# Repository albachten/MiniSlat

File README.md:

# MiniSlat - 2 cue pyro slat

This is an ARM Cortex M0 board with:
* SAMD21 cpu
* USB for programming & serial debug
* Cortex Debug connector for bootloader install & hw debug
* 2 Pairs of PyroClips (2 cues)
* 915MHz HopeRF RFM95 Lora module
* 2S 18650 LiPo supply (two cells in series) with safe/armed power switch
* INA219 current sensing for continuity test & fire monitoring
* 2 NeoPixels as per-cue status indicators
* I2C expansion (QWIIC connector & 4-pin header)

See [SOFTWARE_SPEC.md](SOFTWARE_SPEC.md) for pin assignments, I2C addresses, and firmware requirements.

[Schematic pdf](v1.0/MiniSlat.pdf)

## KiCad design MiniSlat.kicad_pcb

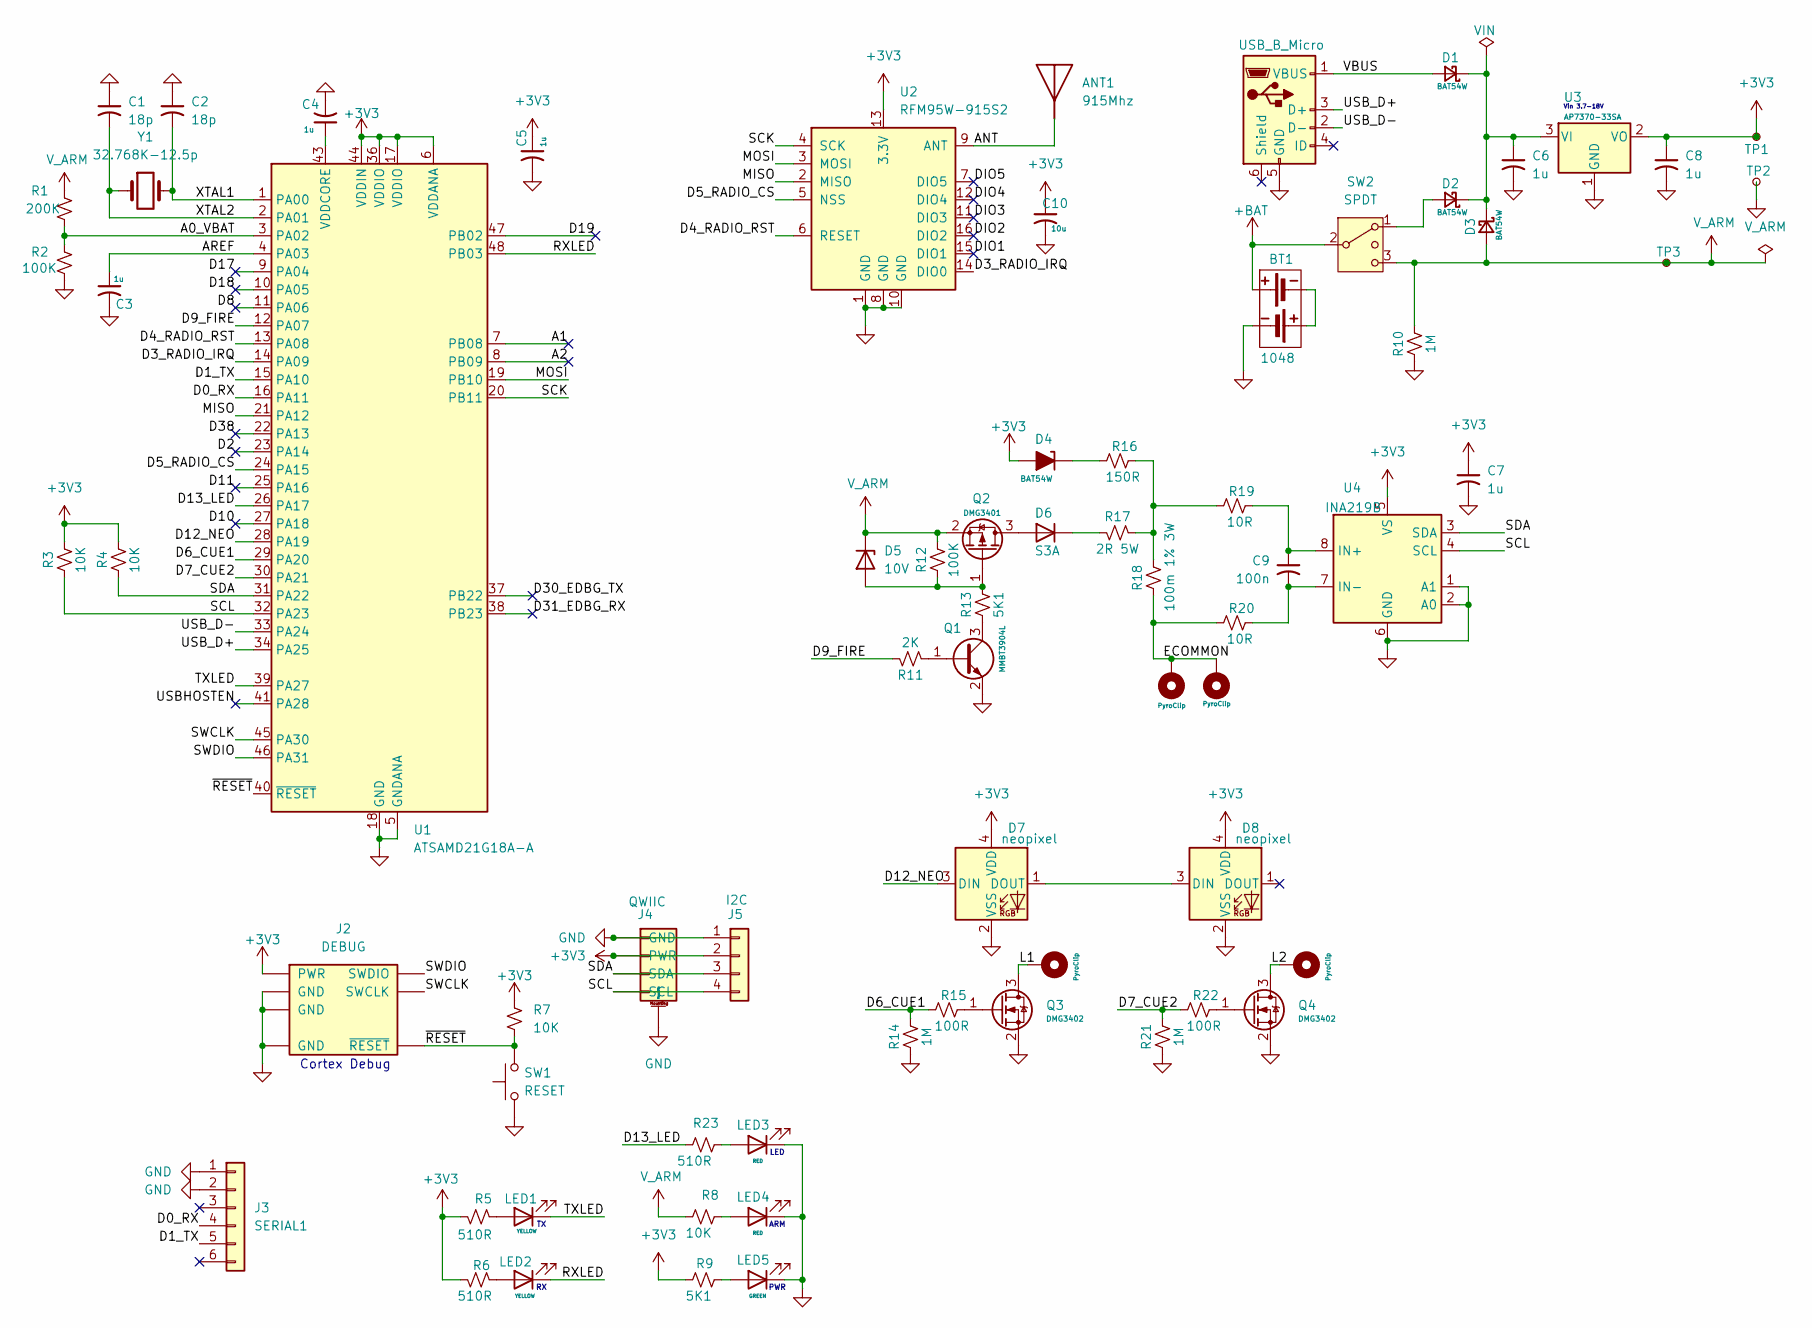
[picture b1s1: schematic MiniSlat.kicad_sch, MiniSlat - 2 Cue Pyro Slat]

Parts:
ANT1: 915Mhz; Antenna915MHzSimpleCoil; Manufacturer_Part_Number 4269; Mouser_Part_Number 485-4269
BT1: 1048; BAT_1048P
C1, C2: 18p; C_0603_1608Metric
C3, C4, C5, C6, C7, C8: 1u; C_0603_1608Metric
C9: 100n; C_0603_1608Metric
C10: 10u; C_0603_1608Metric
CLIP1, CLIP3: PyroClip; PyroClipRed; Mouser_Part_Number N/A
CLIP2, CLIP4: PyroClip; PyroClipBlack; Mouser_Part_Number N/A
D1, D2, D3, D4: BAT54W; D_SOD-123; Mouser_Part_Number 78-BAT54W-HG3-18
D5: 10V; SOT-23; Mouser_Part_Number 863-BZX84C10LT1G
D6: S3A; D_SMC; Mouser_Part_Number 512-S3A
D7, D8: neopixel; LED_WS2812B-2020_PLCC4_2.0x2.0mm
J1: USB_B_Micro; USB_Micro-B_Amphenol_10118194_Horizontal; Mouser_Part_Number 649-10118194-0011LF
J2: DEBUG; CortexDebugSMD; Mouser_Part_Number 640-BD12510A305580LB
J3: SERIAL1; PinHeader_1x06_P2.54mm_Vertical
J4: QWIIC; QWIIC_JST_SH_BM04B-SRSS-TB_1x04-1MP_P1.00mm_Vertical
J5: I2C; PinHeader_1x04_P2.54mm_Vertical
LED1, LED2: YELLOW; LED_0805_2012Metric; Mouser_Part_Number 710-150080YS75000
LED3, LED4: RED; LED_0805_2012Metric; Mouser_Part_Number 710-150080RS75000
LED5: GREEN; LED_0805_2012Metric; Mouser_Part_Number 710-150080RS75000
Q1: MMBT3904L; SOT-23; Mouser_Part_Number 771-MMBT3904VL
Q2: DMG3401; SC-59; Mouser_Part_Number 621-DMP3099L-13
Q3, Q4: DMG3402; SOT-23; Mouser_Part_Number 621-DMG3402L-7
R1: 200K; R_0603_1608Metric
R2, R12: 100K; R_0603_1608Metric
R3, R4, R7, R8: 10K; R_0603_1608Metric
R5, R6, R23: 510R; R_0603_1608Metric
R9, R13: 5K1; R_0603_1608Metric
R10, R14, R21: 1M; R_0603_1608Metric
R11: 2K; R_0603_1608Metric
R15, R22: 100R; R_0603_1608Metric
R16: 150R; R_0603_1608Metric
R17: 2R 5W; R_Axial_Power_L25.0mm_W6.4mm_P27.94mm; Mouser_Part_Number 588-TUW5J2R0E
R18: 100m 1% 3W; R_2512_6332Metric
R19, R20: 10R; R_0603_1608Metric
SW1: RESET; TL3305B_SPST_PushButton; Mouser_Part_Number 652-CR0805JW-104ELF
SW2: SPDT; spdt_100SP1T1B2M2QE
TP1, TP2, TP3: RCTCTE; Mouser_Part_Number 660-RCTCTE
U1: ATSAMD21G18A-A; TQFP-48_7x7mm_P0.5mm; Mouser_Part_Number 556-ATSAMD21G18A-MU
U2: RFM95W-915S2; RFM95CW; Mouser_Part_Number 223-RFM95W-915S2
U3: AP7370-33SA; TSOT-23
U4: INA219B; SOIC-8_3.9x4.9mm_P1.27mm; Mouser_Part_Number 595-INA219BIDR
Y1: 32.768K-12.5p; Crystal_SMD_G8-2Pin_3.2x1.5mm; Mouser_Part_Number 520-327-12.5-34B

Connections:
+3V3: C5.1, C7.1, C8.1, C10.1, D4.2 (A), D7.4 (VDD), D8.4 (VDD), J2.1 (PWR), J4.2 (PWR), J5.2, R3.2, R4.2, R5.1, R6.1, R7.2, R9.1, TP1.1, U1.6 (VDDANA), U1.17 (VDDIO), U1.36 (VDDIO), U1.44 (VDDIN), U2.13 (3.3V), U3.2 (VO), U4.5 (VS)
+BAT: BT1.1, SW2.2 (3)
/A0_VBAT: R1.2, R2.1, U1.3 (PA02)
/A1: U1.7 (PB08)
/A2: U1.8 (PB09)
/ANT: ANT1.1 (A), U2.9 (ANT)
/AREF: C3.1, U1.4 (PA03)
/D0_RX: J3.4, U1.16 (PA11)
/D1_TX: J3.5, U1.15 (PA10)
/D2: U1.23 (PA14)
/D3_RADIO_IRQ: U1.14 (PA09), U2.14 (DIO0)
/D4_RADIO_RST: U1.13 (PA08), U2.6 (RESET)
/D5_RADIO_CS: U1.24 (PA15), U2.5 (NSS)
/D6_CUE1: R14.2, R15.1, U1.29 (PA20)
/D7_CUE2: R21.2, R22.1, U1.30 (PA21)
/D8: U1.11 (PA06)
/D9_FIRE: R11.1, U1.12 (PA07)
/D10: U1.27 (PA18)
/D11: U1.25 (PA16)
/D12_NEO: D7.3 (DIN), U1.28 (PA19)
/D13_LED: R23.1, U1.26 (PA17)
/D17: U1.9 (PA04)
/D18: U1.10 (PA05)
/D19: U1.47 (PB02)
/D30_EDBG_TX: U1.37 (PB22)
/D31_EDBG_RX: U1.38 (PB23)
/D39: U1.22 (PA13)
/DIO1: U2.15 (DIO1)
/DIO2: U2.16 (DIO2)
/DIO3: U2.11 (DIO3)
/DIO4: U2.12 (DIO4)
/DIO5: U2.7 (DIO5)
/ECOMMON: CLIP1.1, CLIP3.1, R18.1, R20.1
/L1: CLIP2.1, Q3.3 (D)
/L2: CLIP4.1, Q4.3 (D)
/MISO: U1.21 (PA12), U2.2 (MISO)
/MOSI: U1.19 (PB10), U2.3 (MOSI)
/RXLED: LED2.1 (K), U1.48 (PB03)
/SCK: U1.20 (PB11), U2.4 (SCK)
/SCL: J4.4 (SCL), J5.4, R3.1, U1.32 (PA23), U4.4 (SCL)
/SDA: J4.3 (SDA), J5.3, R4.1, U1.31 (PA22), U4.3 (SDA)
/SWCLK: J2.4 (SWCLK), U1.45 (PA30)
/SWDIO: J2.2 (SWDIO), U1.46 (PA31)
/TXLED: LED1.1 (K), U1.39 (PA27)
/USBHOSTEN: U1.41 (PA28)
/USB_D+: J1.3 (D+), U1.34 (PA25)
/USB_D-: J1.2 (D-), U1.33 (PA24)
/VBUS: D1.2 (A), J1.1 (VBUS)
/XTAL1: C2.2, U1.1 (PA00), Y1.2
/XTAL2: C1.2, U1.2 (PA01), Y1.1
/~RESET: J2.10 (~RESET), R7.1, SW1.2, U1.40 (~RESET)
GND: BT1.3 (N2), C1.1, C2.1, C3.2, C4.2, C5.2, C6.2, C7.2, C8.2, C10.2, D7.2 (VSS), D8.2 (VSS), J1.5 (GND), J2.3 (GND), J2.5 (GND), J2.9 (GND), J3.1, J3.2, J4.1 (GND), J4.MP (MountPin), J5.1, LED3.1 (K), LED4.1 (K), LED5.1 (K), Q1.2 (E), Q3.2 (S), Q4.2 (S), R2.2, R10.1, R14.1, R21.1, SW1.1, TP2.1, U1.5 (GNDANA), U1.18 (GND), U1.35 (GND), U1.42 (GND), U2.1 (GND), U2.8 (GND), U2.10 (GND), U3.1 (GND), U4.1 (A1), U4.2 (A0), U4.6 (GND)
unnamed: BT1.2 (N1), BT1.4 (P2)
unnamed: C6.1, D1.1 (K), D2.1 (K), D3.1 (K), U3.3 (VI)
unnamed: D2.2 (A), SW2.1
unnamed: D4.1 (K), R16.1
unnamed: D5.1 (A), Q2.1 (G), R12.1, R13.2
unnamed: D6.2 (A), Q2.3 (D)
unnamed: D6.1 (K), R17.2
unnamed: D7.1 (DOUT), D8.3 (DIN)
unnamed: LED1.2 (A), R5.2
unnamed: LED2.2 (A), R6.2
unnamed: LED3.2 (A), R23.2
unnamed: LED4.2 (A), R8.2
unnamed: LED5.2 (A), R9.2
unnamed: Q1.1 (B), R11.2
unnamed: Q1.3 (C), R13.1
unnamed: Q3.1 (G), R15.2
unnamed: Q4.1 (G), R22.2
unnamed: R16.2, R17.1, R18.2, R19.1
unnamed: C4.1, U1.43 (VDDCORE)
unnamed: C9.1, R19.2, U4.8 (IN+)
unnamed: C9.2, R20.2, U4.7 (IN-)
V_ARM: D3.2 (A), D5.3 (K), Q2.2 (S), R1.1, R8.1, R10.2, R12.2, SW2.3 (4), TP3.1

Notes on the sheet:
LED
PWR
ARM
Vin 3.7-18V
Cortex Debug

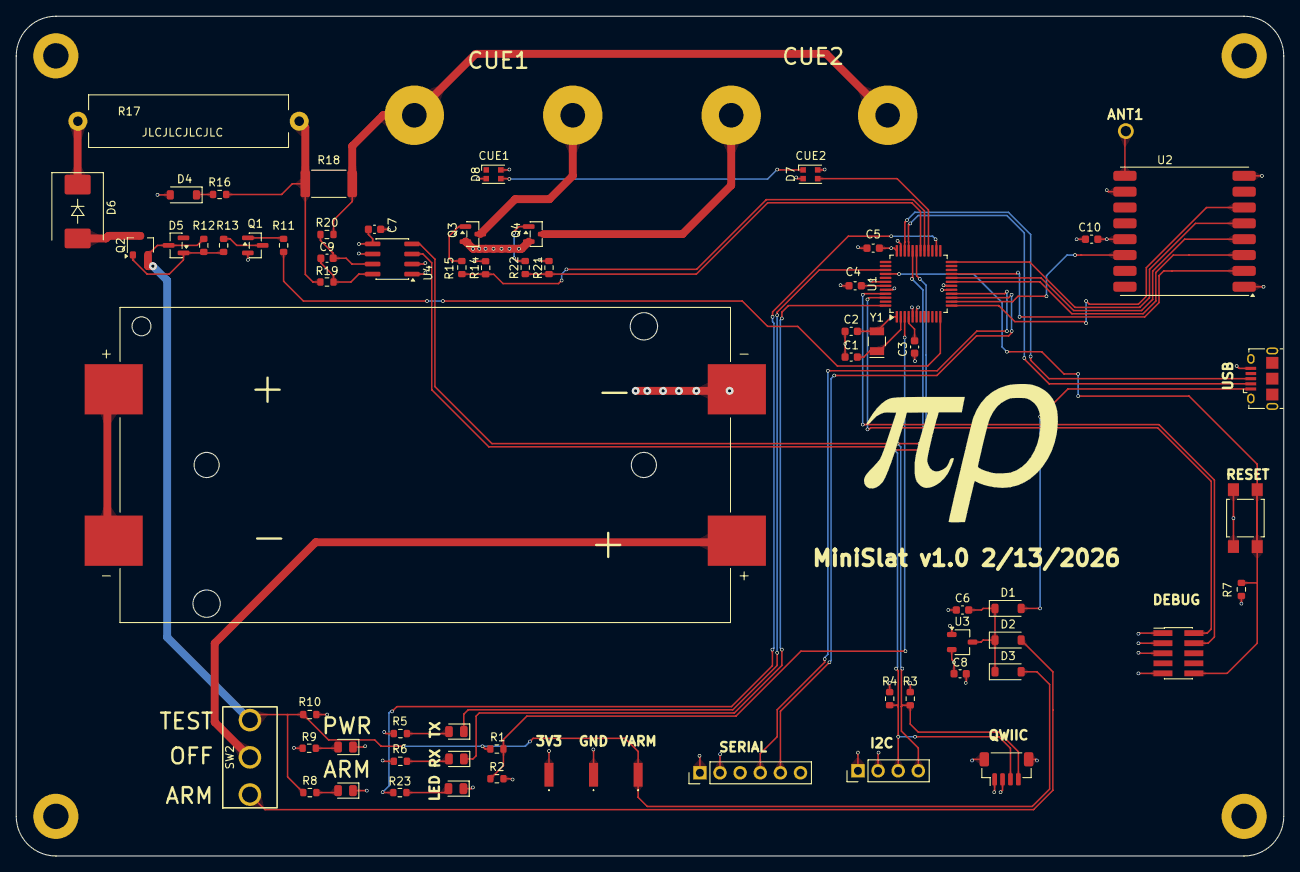
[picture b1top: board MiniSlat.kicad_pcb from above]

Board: 4 copper layers, 160.0 x 106.0 mm, 77 parts (1 on the bottom side), 56 nets.

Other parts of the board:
H1, H2, H3, H4: MountingHole_3.2mm_M3_ISO7380_Pad
LOGO1, LOGO2: LOGO; pirho
